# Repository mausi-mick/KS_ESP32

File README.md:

Kennlinienschreiber mit ESP32

Hier möchte ich nur kurz die ESP32-Variante vorstellen.

Die vorher beschriebenen Versionen  -  auf Arduino NANO / ATMega328P   bzw. Arduino-EVERY basierend   - waren im Laufe der Entwicklung in mehrerer Hinsicht an ihre Grenzen gestossen:

    •     zu wenig Speicher
    •     zu wenig Pins
    •     relativ langsam
    •     Bluetooth nur über externe HW (HC05 /HC12)

Die ersten Tests waren dann aber etwas ernüchternd,  

Gerade die verwandten ADC’s (MCP3204) und DAC’s MCP4822 an SPI (VSPI) machten
Probleme., aber das scheint gelöst zu sein.

Ich verwende ein ESP-Modul mit 38 Pins, um möglichst viele Pins zur Verfügung zu haben für
die BUSSE (I2C, SPI), Schalter und Encoder und  RX/TX (z.B. zur Verbindung mit modif. Transistortester)

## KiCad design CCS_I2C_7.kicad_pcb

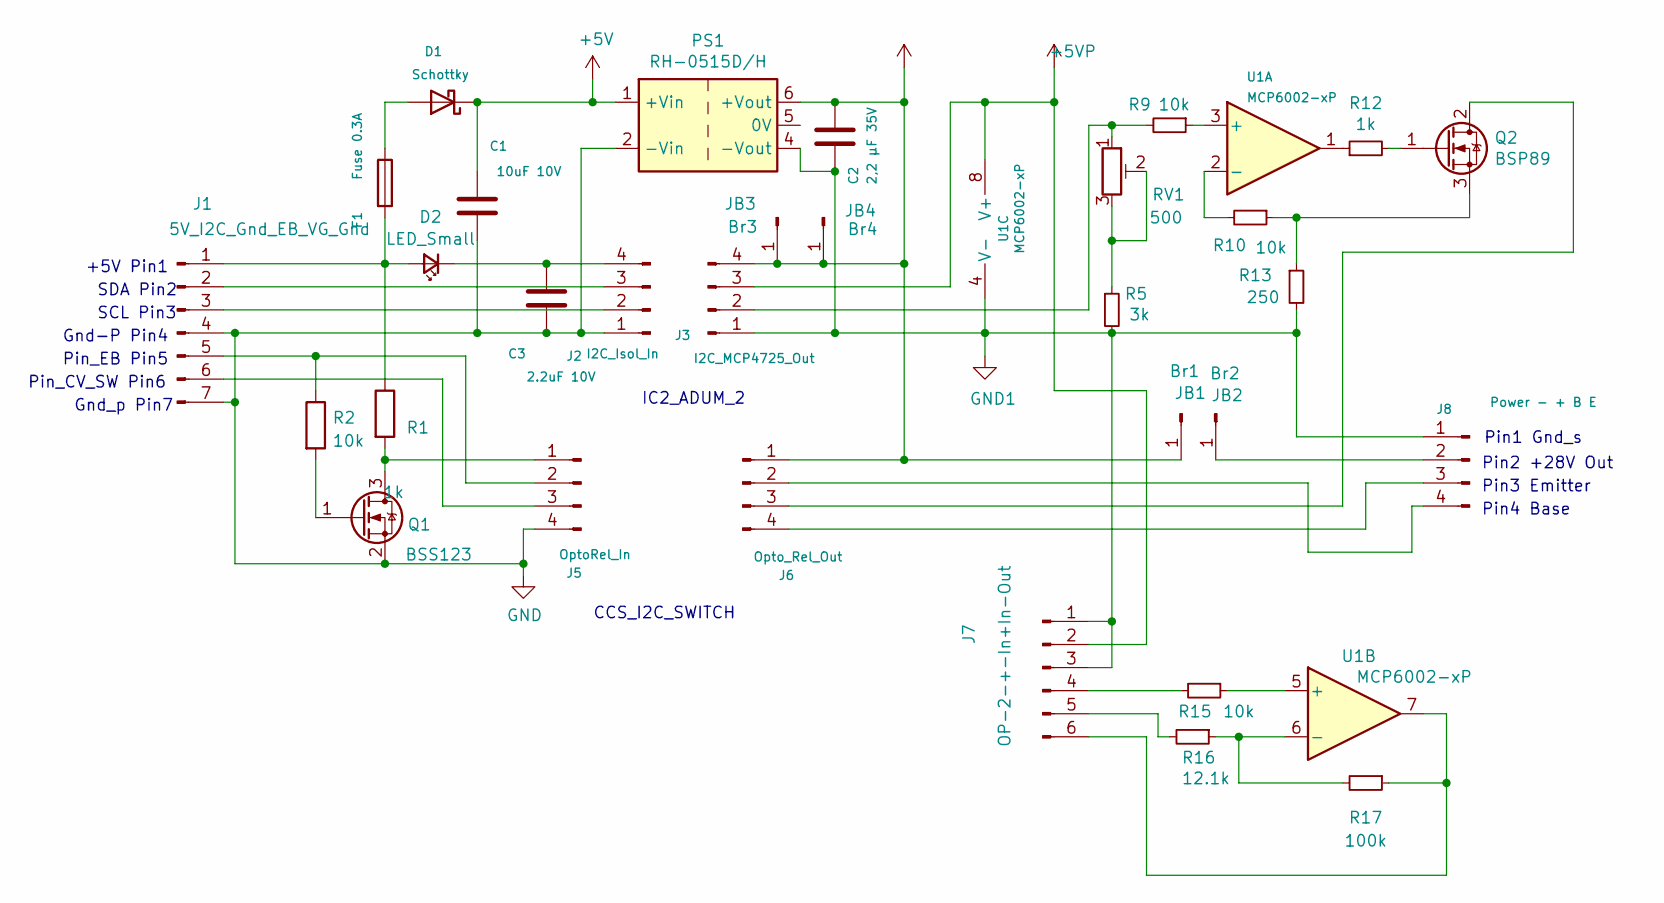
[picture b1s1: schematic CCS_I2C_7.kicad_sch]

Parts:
C1: 10uF 10V; C_1812_4532Metric_Pad1.57x3.40mm_HandSolder
C2: 2,2 µF 35V; C_1812_4532Metric_Pad1.57x3.40mm_HandSolder
C3: 2.2uF 10V; C_1206_3216Metric_Pad1.33x1.80mm_HandSolder
D1: Schottky; D_1206_3216Metric_Pad1.42x1.75mm_HandSolder
D2: LED_Small; LED_D3.0mm
F1: Fuse 0.3A; Fuse_1206_3216Metric_Pad1.42x1.75mm_HandSolder
J1: 5V_I2C_Gnd_EB_VG_Gnd; PinHeader_1x07_P2.54mm_Horizontal
J2: I2C_Isol_In; PinSocket_1x04_P2.54mm_Vertical
J3: I2C_MCP4725_Out; PinSocket_1x04_P2.54mm_Vertical
J5: OptoRel_In; PinSocket_1x04_P2.54mm_Vertical
J6: Opto_Rel_Out; PinSocket_1x04_P2.54mm_Vertical
J7: OP-2-+-In+In-Out; PinHeader_1x06_P2.54mm_Horizontal
J8: Power - + B E; PinHeader_1x04_P2.54mm_Horizontal
JB1: Br1; PinHeader_1x01_P2.54mm_Vertical
JB2: Br2; PinHeader_1x01_P2.54mm_Vertical
JB3: Br3; PinHeader_1x01_P2.54mm_Vertical
JB4: Br4; PinHeader_1x01_P2.54mm_Vertical
PS1: RH-0515D/H; Converter_DCDC_XP_POWER-IHxxxxSH_THT
Q1: BSS123; SOT-23
Q2: BSP89; SOT-223-3_TabPin2
R1: 1k; R_2010_5025Metric_Pad1.40x2.65mm_HandSolder
R2: 10k; R_1206_3216Metric_Pad1.30x1.75mm_HandSolder
R5: 3k; R_Axial_DIN0207_L6.3mm_D2.5mm_P10.16mm_Horizontal
R9, R10, R15: 10k; R_Axial_DIN0207_L6.3mm_D2.5mm_P10.16mm_Horizontal
R12: 1k; R_Axial_DIN0207_L6.3mm_D2.5mm_P10.16mm_Horizontal
R13: 250; R_Axial_DIN0207_L6.3mm_D2.5mm_P10.16mm_Horizontal
R16: 12.1k; R_Axial_DIN0207_L6.3mm_D2.5mm_P10.16mm_Horizontal
R17: 100k; R_Axial_DIN0207_L6.3mm_D2.5mm_P10.16mm_Horizontal
RV1: 500; Potentiometer_ACP_CA6-H2,5_Horizontal
U1: MCP6002-xP; DIP-8_W7.62mm_LongPads

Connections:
+5V: C1.1, D1.1 (K), PS1.1 (+Vin)
+5VP: J3.3, J7.2, U1.8 (V+)
+28V: C2.1, J3.4, J6.1, JB1.1, JB3.1, JB4.1, PS1.6 (+Vout)
GND: C1.2, C3.2, J1.4, J1.7, J2.1, J5.4, PS1.2 (-Vin), Q1.2 (S)
GND1: C2.2, J3.1, J7.1, J7.3, J8.1, PS1.4 (-Vout), R5.2, R13.2, U1.4 (V-)
unnamed: D1.2 (A), F1.1
unnamed: D2.2 (A), F1.2, J1.1, R1.1
unnamed: C3.1, D2.1 (K), J2.4
unnamed: J1.2, J2.3
unnamed: J1.3, J2.2
unnamed: J1.5, J5.2, R2.1
unnamed: J1.6, J5.3
unnamed: J3.2, R9.2, RV1.1
unnamed: J5.1, Q1.3 (D), R1.2
unnamed: J6.2, J8.4
unnamed: J6.3, Q2.2 (D)
unnamed: J6.4, J8.3
unnamed: J7.4, R15.2
unnamed: J7.5, R16.2
unnamed: J7.6, R17.1, U1.7
unnamed: J8.2, JB2.1
unnamed: Q1.1 (G), R2.2
unnamed: Q2.1 (G), R12.2
unnamed: Q2.3 (S), R10.1, R13.1
unnamed: R5.1, RV1.2, RV1.3
unnamed: R12.1, U1.1
unnamed: R9.1, U1.3 (+)
unnamed: R10.2, U1.2 (-)
unnamed: R15.1, U1.5 (+)
unnamed: R16.1, R17.2, U1.6 (-)

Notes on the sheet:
Pin_EB Pin5
IC2_ADUM_2
+5V Pin1
Gnd-P Pin4
SDA Pin2
Pin2 +28V Out
SCL Pin3
Pin4 Base
Gnd_p Pin7
Pin1 Gnd_s
Pin3 Emitter
CCS_I2C_SWITCH
Pin_CV_SW Pin6

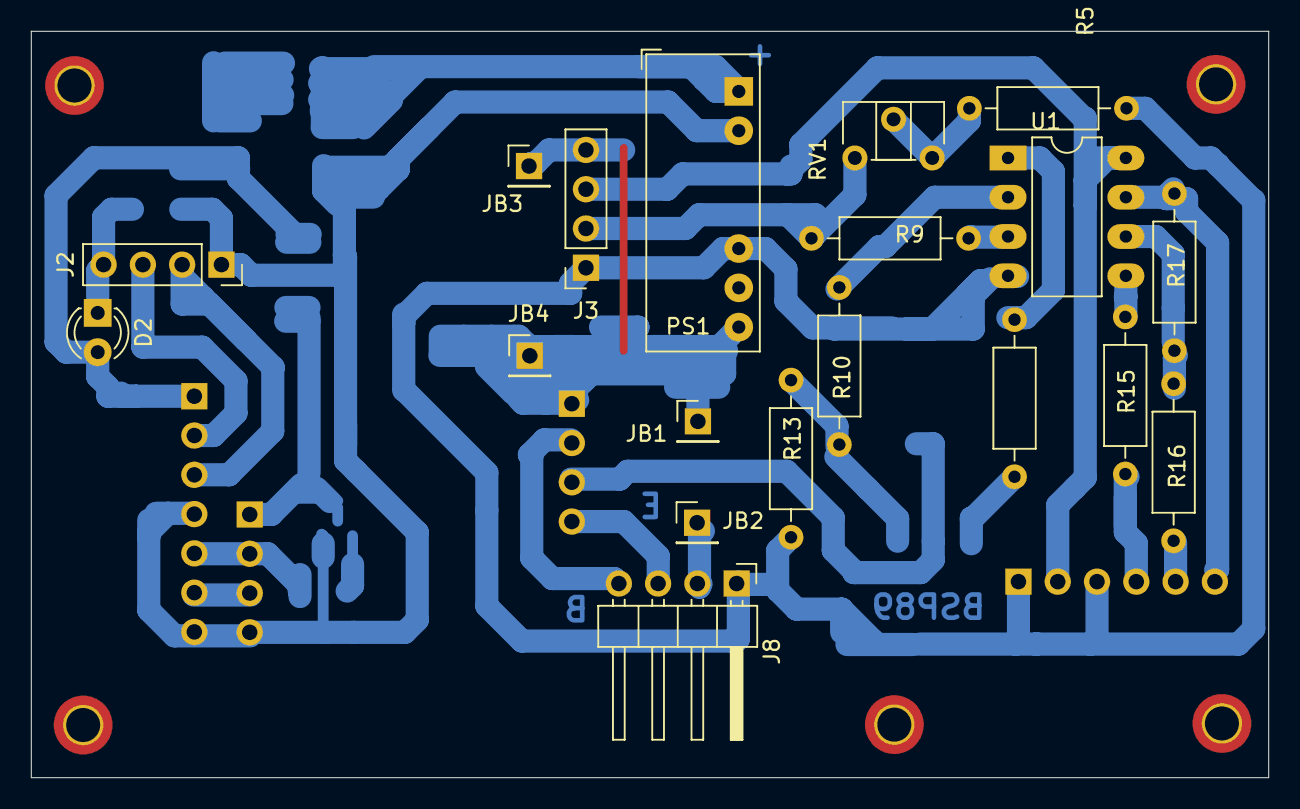
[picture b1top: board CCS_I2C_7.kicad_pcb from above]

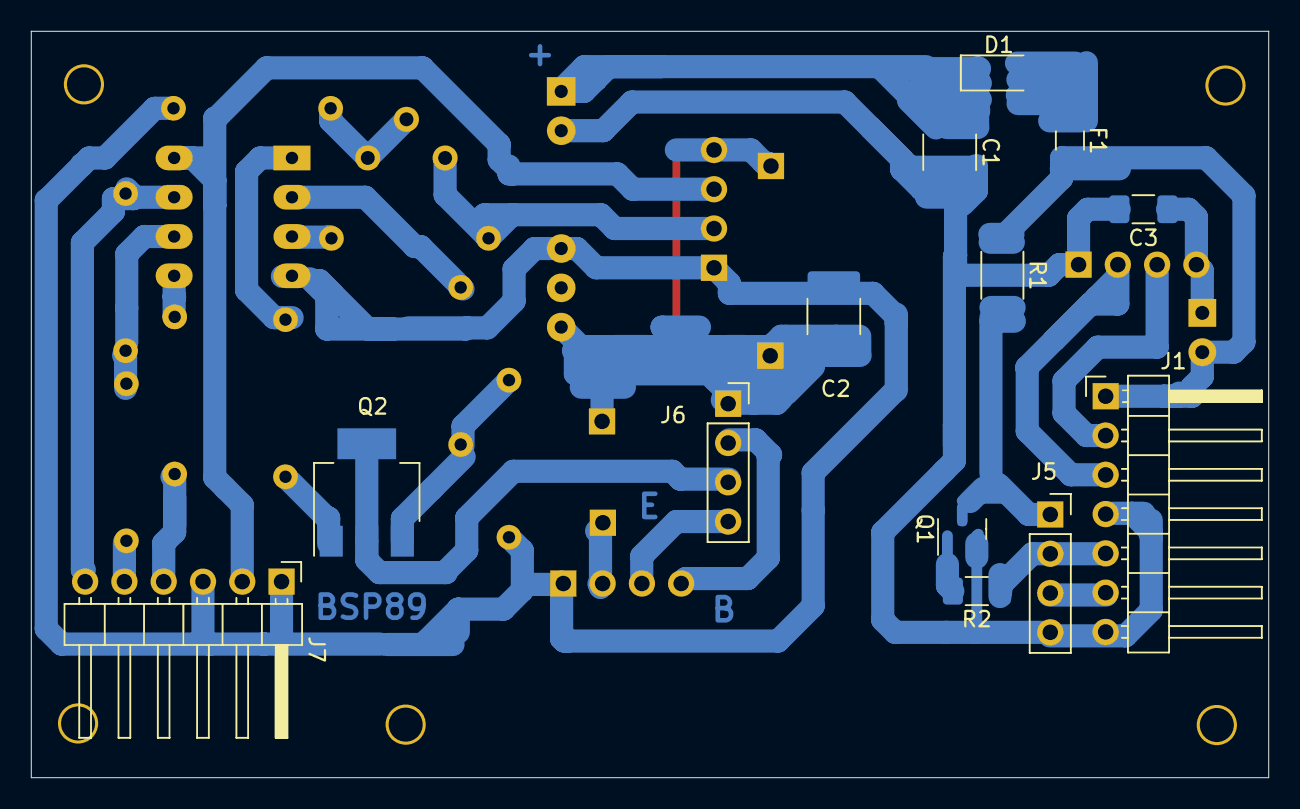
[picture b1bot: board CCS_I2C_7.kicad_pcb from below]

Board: 2 copper layers, 80.0 x 48.3 mm, 32 parts (13 on the bottom side), 30 nets.

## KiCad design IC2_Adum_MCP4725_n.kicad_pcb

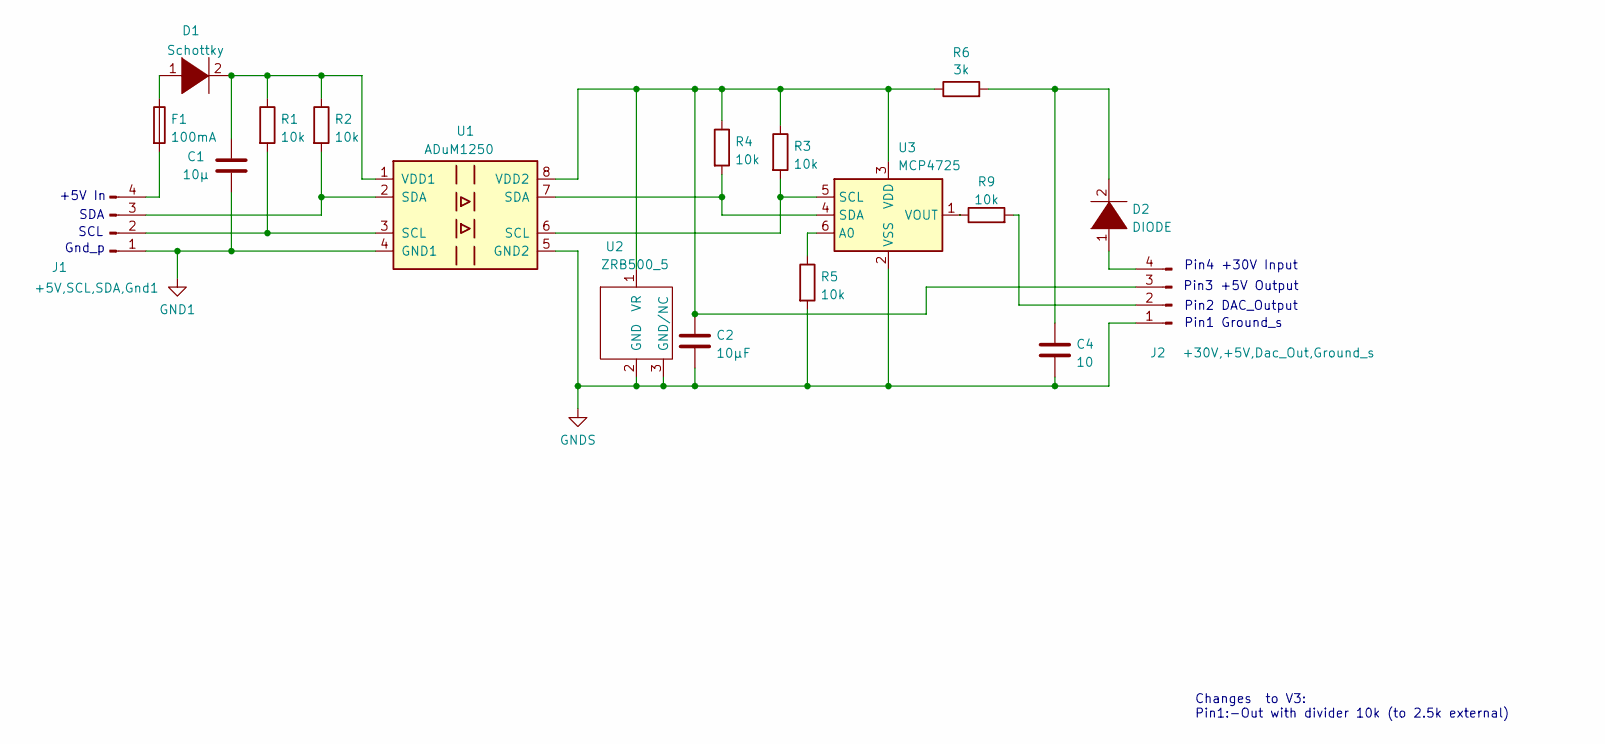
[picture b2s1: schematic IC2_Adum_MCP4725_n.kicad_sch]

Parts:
C1: 10µ; C_1206_3216Metric_Pad1.33x1.80mm_HandSolder
C2: 10µF; C_1206_3216Metric_Pad1.33x1.80mm_HandSolder
C4: 10; C_1206_3216Metric_Pad1.33x1.80mm_HandSolder
D1: Schottky; D_1206_3216Metric_Pad1.42x1.75mm_HandSolder
D2: DIODE; D_0805_2012Metric_Pad1.15x1.40mm_HandSolder
F1: 100mA; Fuse_1206_3216Metric_Pad1.42x1.75mm_HandSolder
J1: +5V,SCL,SDA,Gnd1; PinHeader_1x04_P2.54mm_Vertical
J2: +30V,+5V,Dac_Out,Ground_s; PinHeader_1x04_P2.54mm_Vertical
R1, R2, R3, R4, R5, R9: 10k; R_1206_3216Metric_Pad1.30x1.75mm_HandSolder
R6: 3k; R_1206_3216Metric_Pad1.30x1.75mm_HandSolder
U1: ADuM1250; SOIC-8_3.9x4.9mm_P1.27mm
U2: ZRB500_5; SOT-23-3
U3: MCP4725; SOT-23-6

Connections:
GND1: C1.2, J1.1, U1.4 (GND1)
GNDS: C2.2, C4.2, J2.1, R5.2, U1.5 (GND2), U2.2 (GND), U2.3 (GND/NC), U3.2 (VSS)
unnamed: C1.1, D1.2 (A), R1.1, R2.1, U1.1 (VDD1)
unnamed: D1.1 (K), F1.1
unnamed: C4.1, D2.2 (A), R6.2
unnamed: D2.1 (K), J2.4
unnamed: J1.2, R1.2, U1.3 (SCL)
unnamed: J1.3, R2.2, U1.2 (SDA)
unnamed: F1.2, J1.4
unnamed: J2.2, R9.2
unnamed: C2.1, J2.3, R3.1, R4.1, R6.1, U1.8 (VDD2), U2.1 (VR), U3.3 (VDD)
unnamed: R5.1, U3.6 (A0)
unnamed: R3.2, U1.6 (SCL), U3.5 (SCL)
unnamed: R4.2, U1.7 (SDA), U3.4 (SDA)
unnamed: R9.1, U3.1 (VOUT)

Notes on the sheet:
Pin2 DAC_Output
Changes to V3: Pin1:-Out with divider 10k (to 2.5k external)
+5V In
Pin3 +5V Output
Gnd_p
SDA
Pin1 Ground_s
SCL
Pin4 +30V Input

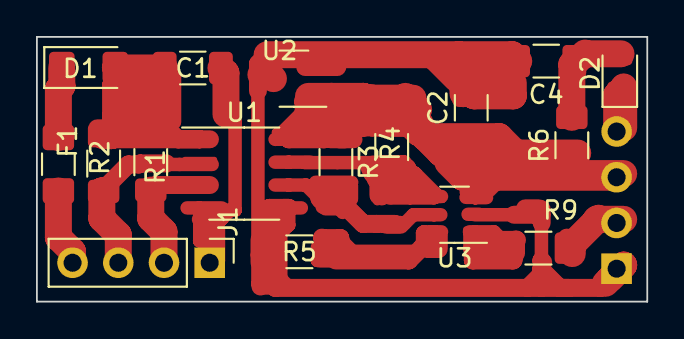
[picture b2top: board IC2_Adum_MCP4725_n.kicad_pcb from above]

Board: 2 copper layers, 33.9 x 14.7 mm, 18 parts (1 on the bottom side), 15 nets.

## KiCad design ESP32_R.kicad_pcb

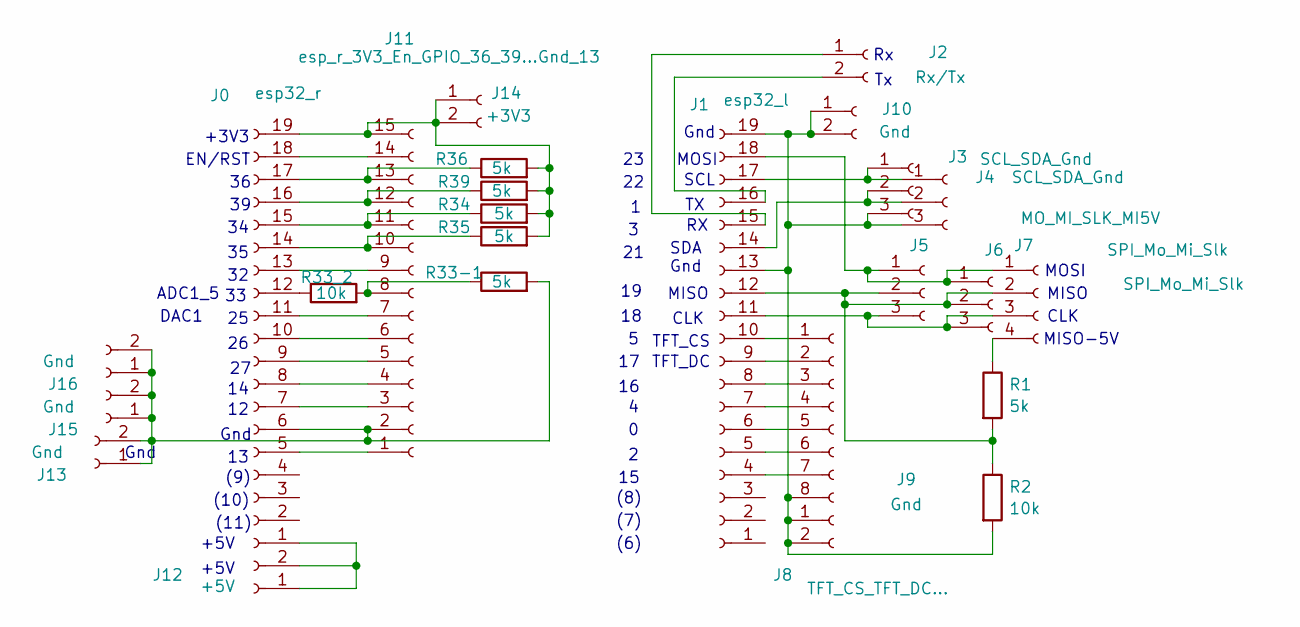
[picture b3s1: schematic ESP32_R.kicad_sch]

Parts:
J0: esp32_r; PinSocket_1x19_P2.54mm_Vertical
J1: esp32_l; PinSocket_1x19_P2.54mm_Vertical
J2: Rx/Tx; PinSocket_1x02_P2.54mm_Vertical
J3, J4: SCL_SDA_Gnd; PinSocket_1x03_P2.54mm_Vertical
J5, J6: SPI_Mo_Mi_Slk; PinSocket_1x03_P2.54mm_Vertical
J7: MO_MI_SLK_MI5V; PinHeader_1x04_P2.54mm_Vertical
J8: TFT_CS_TFT_DC...; PinSocket_1x08_P2.54mm_Vertical
J9, J10, J13, J15, J16: Gnd; PinSocket_1x02_P2.54mm_Vertical
J11: esp_r_3V3_En_GPIO_36_39...Gnd_13; PinHeader_1x15_P2.54mm_Vertical
J12: +5V; PinSocket_1x02_P2.54mm_Vertical
J14: +3V3; PinSocket_1x02_P2.54mm_Vertical
R1, R33-1, R34, R35, R36, R39: 5k; R_1206_3216Metric_Pad1.30x1.75mm_HandSolder
R2: 10k; R_1206_3216Metric_Pad1.30x1.75mm_HandSolder
R33_2: 10k; R_0603_1608Metric_Pad0.98x0.95mm_HandSolder

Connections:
unnamed: J0.1, J12.1, J12.2
unnamed: J0.5, J11.1
unnamed: J0.6, J11.2, J13.1, J13.2, J15.1, J15.2, J16.1, J16.2, R33-1.2
unnamed: J0.7, J11.3
unnamed: J0.8, J11.4
unnamed: J0.9, J11.5
unnamed: J0.10, J11.6
unnamed: J0.11, J11.7
unnamed: J0.12, R33_2.1
unnamed: J0.13, J11.9
unnamed: J0.14, J11.10, R35.1
unnamed: J0.15, J11.11, R34.1
unnamed: J0.16, J11.12, R39.1
unnamed: J0.17, J11.13, R36.1
unnamed: J0.18, J11.14
unnamed: J0.19, J11.15, J14.1, J14.2, R34.2, R35.2, R36.2, R39.2
unnamed: J1.4, J8.7
unnamed: J1.5, J8.6
unnamed: J1.6, J8.5
unnamed: J1.7, J8.4
unnamed: J1.8, J8.3
unnamed: J1.9, J8.2
unnamed: J1.10, J8.1
unnamed: J1.11, J5.3, J6.3, J7.3
unnamed: J1.12, J5.2, J6.2, J7.2, R1.2, R2.1
unnamed: J1.13, J1.19, J3.3, J4.3, J8.8, J9.1, J9.2, J10.1, J10.2, R2.2
unnamed: J1.14, J3.2, J4.2
unnamed: J1.15, J2.1
unnamed: J1.16, J2.2
unnamed: J1.17, J3.1, J4.1
unnamed: J1.18, J5.1, J6.1, J7.1
unnamed: J7.4, R1.1
unnamed: J11.8, R33-1.1, R33_2.2

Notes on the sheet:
Gnd
EN/RST
MOSI
TFT_CS
(10)
ADC1_5
MISO-5V
CLK
(6)
DAC1
(7)
(11)
TFT_DC
MISO
(8)
(9)
SDA
SCL
+3V3
+5V

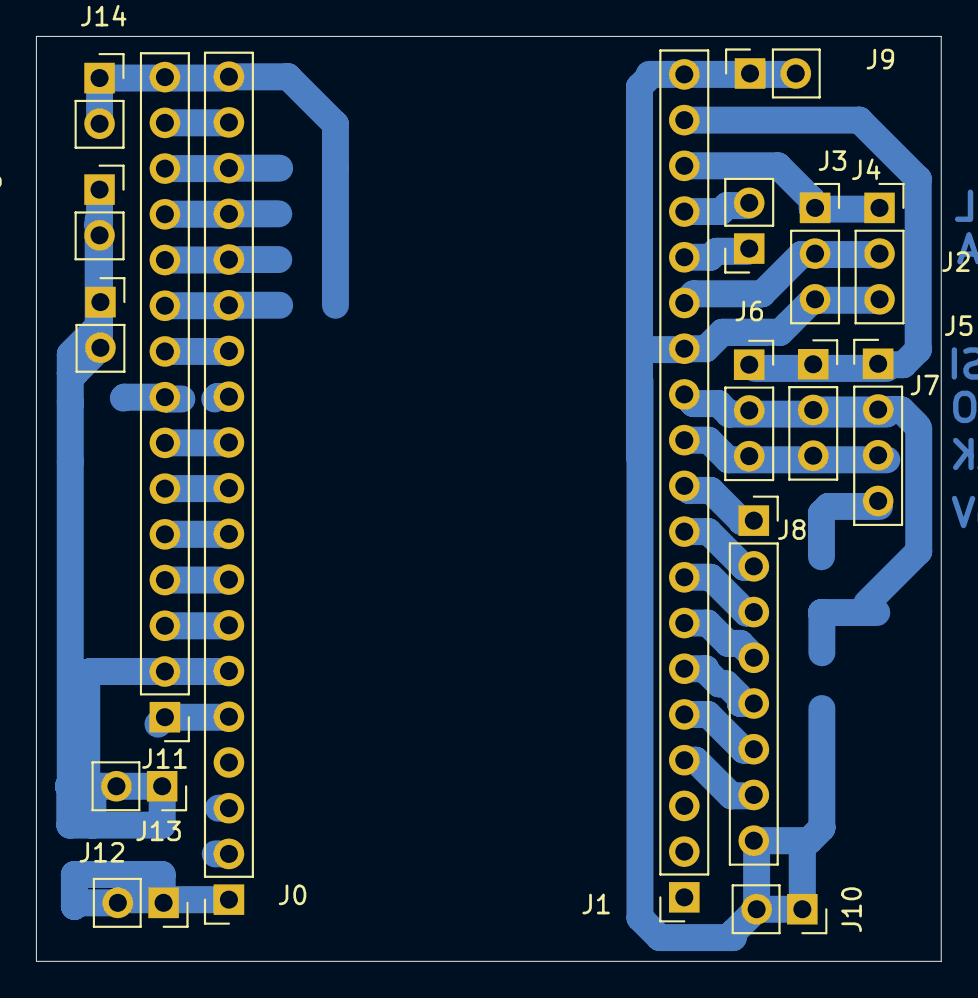
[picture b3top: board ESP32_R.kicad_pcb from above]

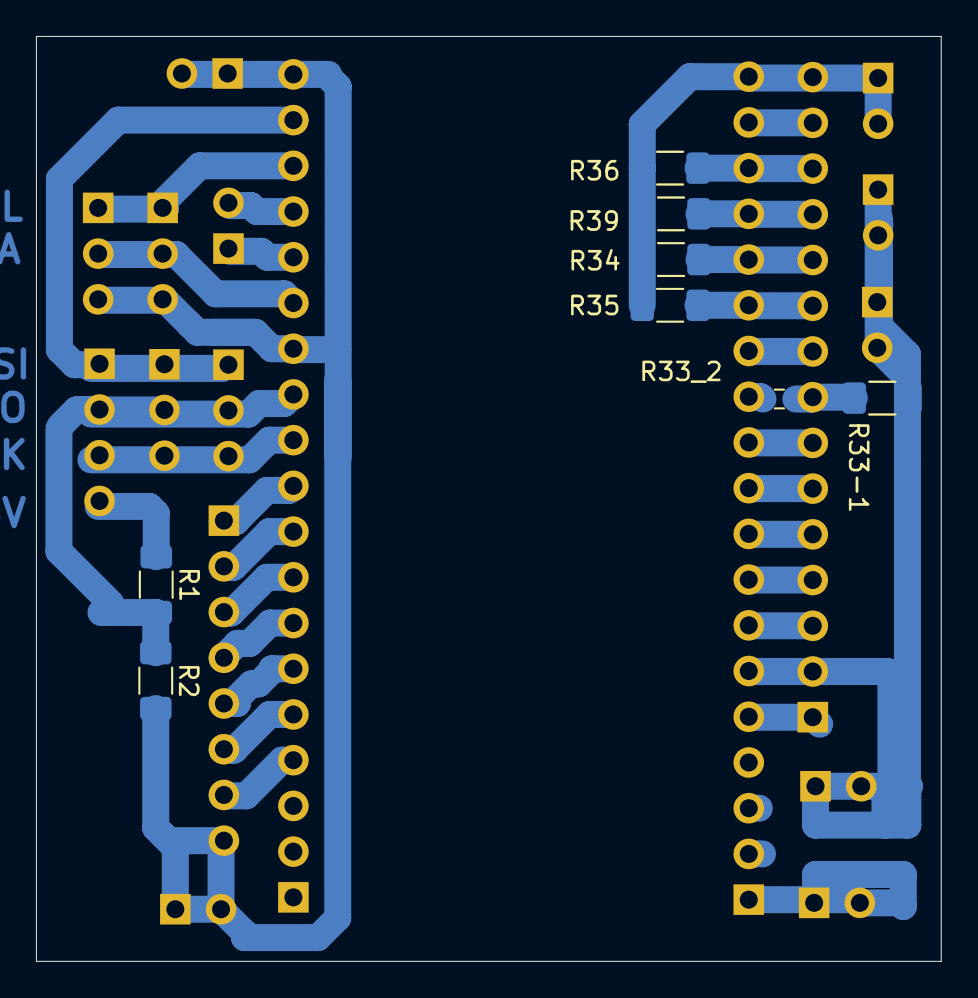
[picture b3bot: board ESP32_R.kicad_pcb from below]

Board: 2 copper layers, 50.3 x 51.4 mm, 25 parts (8 on the bottom side), 33 nets.

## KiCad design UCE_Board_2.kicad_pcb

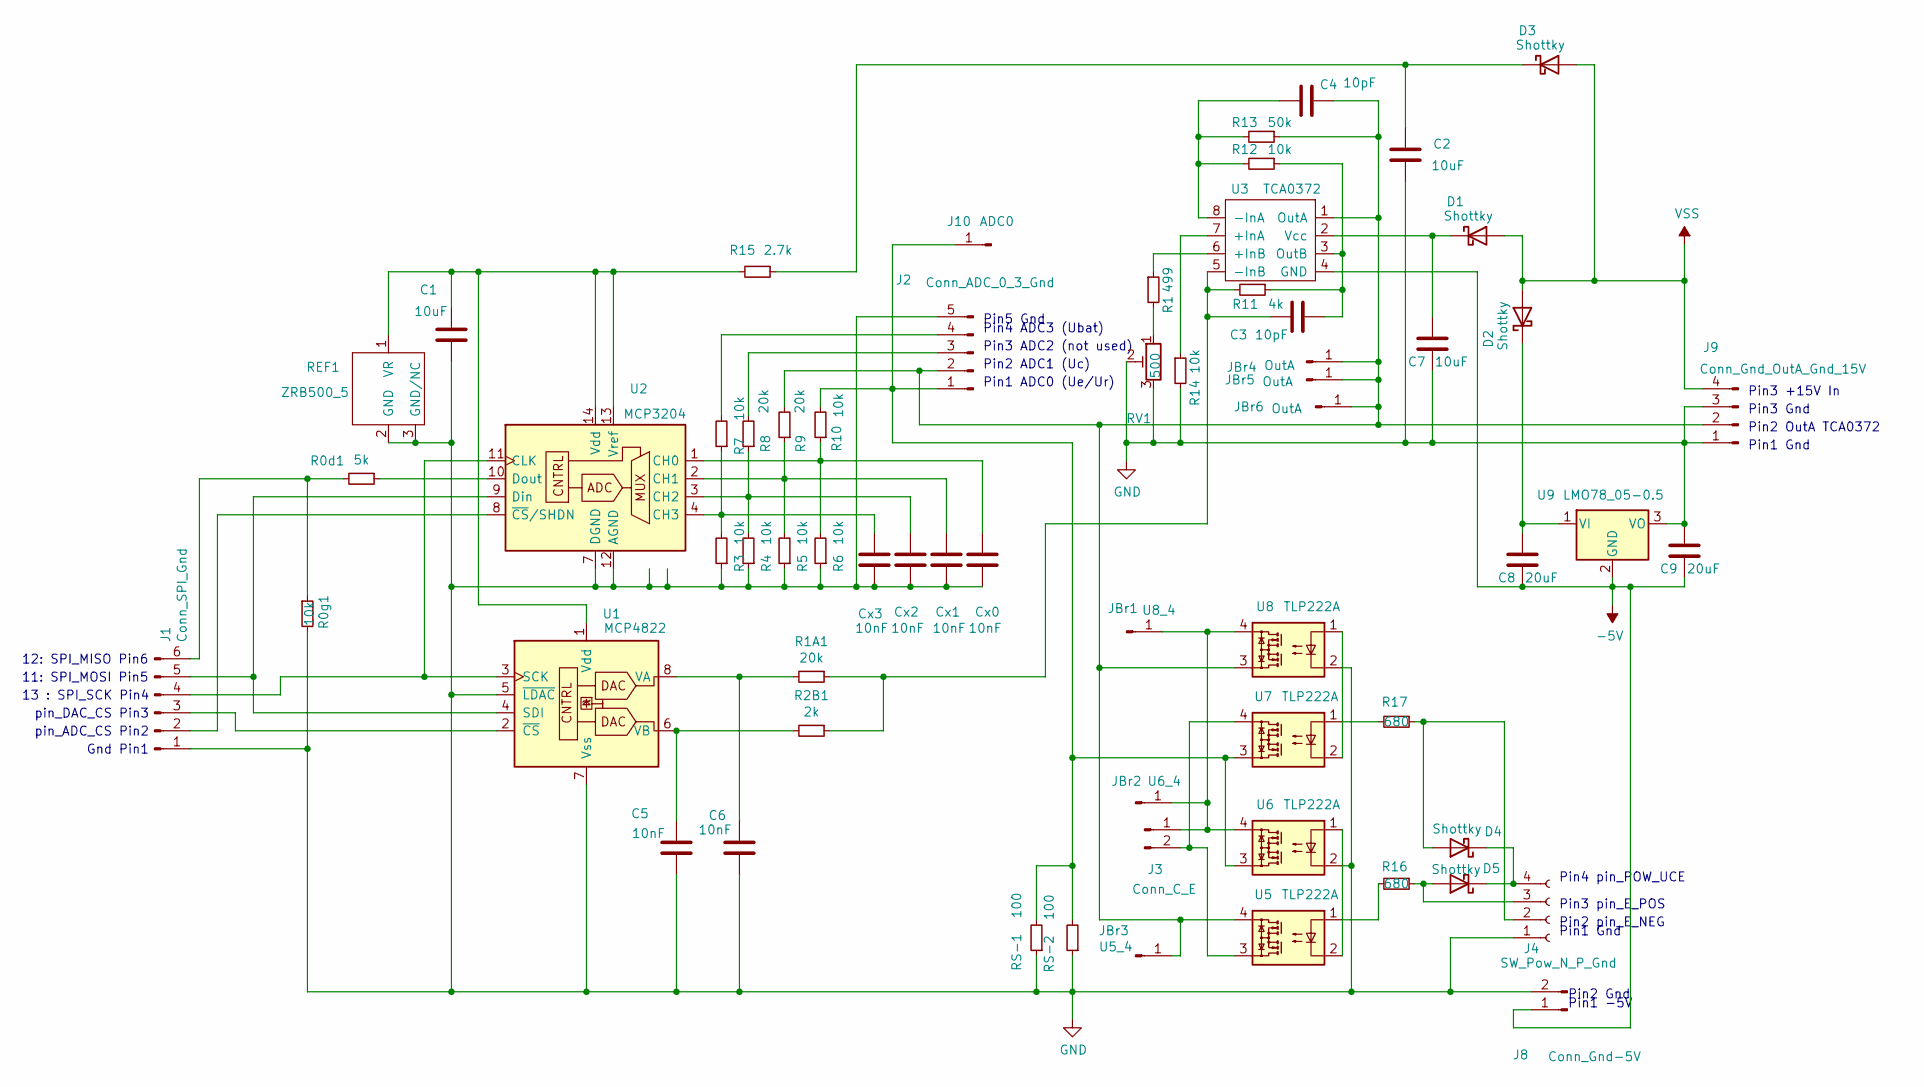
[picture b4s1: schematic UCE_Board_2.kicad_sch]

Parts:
C1: 10uF; C_1210_3225Metric_Pad1.33x2.70mm_HandSolder
C2: 10uF; C_1812_4532Metric_Pad1.57x3.40mm_HandSolder
C3: 10pF; C_Axial_L5.1mm_D3.1mm_P7.50mm_Horizontal
C4: 10pF; C_Rect_L9.0mm_W2.5mm_P7.50mm_MKT
C5, C6: 10nF; C_1206_3216Metric_Pad1.33x1.80mm_HandSolder
C7: 10uF; C_1206_3216Metric_Pad1.33x1.80mm_HandSolder
C8, C9: 20uF; C_1812_4532Metric_Pad1.57x3.40mm_HandSolder
Cx0, Cx1, Cx2, Cx3: 10nF; C_0805_2012Metric_Pad1.18x1.45mm_HandSolder
D1, D2, D3: Shottky; D_1206_3216Metric_Pad1.42x1.75mm_HandSolder
D4, D5: Shottky; D_0603_1608Metric_Pad1.05x0.95mm_HandSolder
J1: Conn_SPI_Gnd; PinHeader_1x06_P2.54mm_Horizontal
J2: Conn_ADC_0_3_Gnd; PinHeader_1x05_P2.54mm_Vertical
J3: Conn_C_E; PinHeader_1x02_P2.54mm_Horizontal
J4: SW_Pow_N_P_Gnd; PinHeader_1x04_P2.54mm_Horizontal
J8: Conn_Gnd-5V; PinHeader_1x02_P2.54mm_Vertical
J9: Conn_Gnd_OutA_Gnd_15V; PinHeader_1x04_P2.54mm_Horizontal
J10: ADC0; PinHeader_1x01_P2.54mm_Vertical
JBr1: U8_4; PinHeader_1x01_P2.54mm_Vertical
JBr2: U6_4; PinHeader_1x01_P2.54mm_Vertical
JBr3: U5_4; PinHeader_1x01_P1.00mm_Vertical
JBr4: OutA; PinHeader_1x01_P1.00mm_Vertical
JBr5, JBr6: OutA; PinHeader_1x01_P1.27mm_Vertical
R0d1: 5k; R_1206_3216Metric_Pad1.30x1.75mm_HandSolder
R0g1, R12: 10k; R_Axial_DIN0204_L3.6mm_D1.6mm_P7.62mm_Horizontal
R1: 499; R_Axial_DIN0207_L6.3mm_D2.5mm_P10.16mm_Horizontal
R1A1: 20k; R_Axial_DIN0207_L6.3mm_D2.5mm_P10.16mm_Horizontal
R2B1: 2k; R_Axial_DIN0207_L6.3mm_D2.5mm_P10.16mm_Horizontal
R3, R4, R5, R6, R7, R10: 10k; R_1206_3216Metric_Pad1.30x1.75mm_HandSolder
R8, R9: 20k; R_1206_3216Metric_Pad1.30x1.75mm_HandSolder
R11: 4k; R_Axial_DIN0207_L6.3mm_D2.5mm_P10.16mm_Horizontal
R13: 50k; R_Axial_DIN0207_L6.3mm_D2.5mm_P10.16mm_Horizontal
R14: 10k; R_Axial_DIN0207_L6.3mm_D2.5mm_P10.16mm_Horizontal
R15: 2.7k; R_Axial_DIN0207_L6.3mm_D2.5mm_P10.16mm_Horizontal
R16, R17: 680; R_Axial_DIN0207_L6.3mm_D2.5mm_P10.16mm_Horizontal
REF1: ZRB500_5; SOT-23
RS-1, RS-2: 100; R_Axial_DIN0207_L6.3mm_D2.5mm_P10.16mm_Horizontal
RV1: 500; Potentiometer_ACP_CA9-H2,5_Horizontal
U1: MCP4822; DIP-8_W7.62mm_LongPads
U2: MCP3204; DIP-14_W7.62mm
U3: TCA0372; DIP-8_W7.62mm_LongPads
U5, U6, U7, U8: TLP222A; DIP-4_W7.62mm
U9: LMO78_05-0.5; TO-220-3_Vertical

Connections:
-5V: C8.2, C9.2, J8.1, U3.4 (GND), U9.2 (GND)
GND: C1.2, C2.2, C5.1, C6.1, C7.2, C9.1, Cx0.1, Cx1.1, Cx2.1, Cx3.1, J1.1, J2.5, J4.1, J8.2, J9.1, J9.3, R0g1.2, R3.1, R4.1, R5.1, R6.1, R14.2, REF1.2 (GND), REF1.3 (GND/NC), RS-1.1, RS-2.1, RV1.2, RV1.3, U1.5 (~LDAC), U1.7 (Vss), U2.5 (NC), U2.6 (NC), U2.7 (DGND), U2.12 (AGND), U6.2, U8.2, U9.3 (VO)
unnamed: C7.1, D1.1 (K), U3.2 (Vcc)
unnamed: C8.1, D2.1 (K), U9.1 (VI)
unnamed: C2.1, D3.1 (K), R15.1
unnamed: D4.2 (A), J4.2, R17.1
unnamed: D4.1 (K), D5.1 (K), J4.4
unnamed: D5.2 (A), J4.3, R16.1
unnamed: J1.2, U2.8 (~CS/SHDN)
unnamed: J1.3, U1.2 (~CS)
unnamed: J1.4, U1.3 (SCK), U2.11 (CLK)
unnamed: J1.5, U1.4 (SDI), U2.9 (Din)
unnamed: J1.6, R0d1.2, R0g1.1
unnamed: C4.1, J2.2, J9.2, JBr3.1, JBr4.1, JBr5.1, JBr6.1, R9.2, R13.1, U3.1 (OutA), U5.4, U8.3
unnamed: J2.3, R8.2
unnamed: J2.4, R7.2
unnamed: J3.1, JBr1.1, JBr2.1, U6.4, U8.4
unnamed: J3.2, U5.3, U7.4
unnamed: J2.1, J10.1, R10.2, RS-1.2, RS-2.2, U6.3, U7.3
unnamed: R1.2, RV1.1
unnamed: R16.2, U5.1
unnamed: R17.2, U7.1
unnamed: C1.1, R15.2, REF1.1 (VR), U1.1 (Vdd), U2.13 (Vref), U2.14 (Vdd)
unnamed: C6.2, R1A1.2, U1.8 (VA)
unnamed: C5.2, R2B1.2, U1.6 (VB)
unnamed: Cx0.2, R6.2, R10.1, U2.1 (CH0)
unnamed: Cx1.2, R5.2, R9.1, U2.2 (CH1)
unnamed: Cx2.2, R4.2, R8.1, U2.3 (CH2)
unnamed: Cx3.2, R3.2, R7.1, U2.4 (CH3)
unnamed: R0d1.1, U2.10 (Dout)
unnamed: R14.1, U3.7 (+InA)
unnamed: R1.1, U3.6 (+InB)
unnamed: C4.2, R12.2, R13.2, U3.8 (-InA)
unnamed: C3.2, R1A1.1, R2B1.1, R11.2, U3.5 (-InB)
unnamed: C3.1, R11.1, R12.1, U3.3 (OutB)
unnamed: U5.2, U6.1
unnamed: U7.2, U8.1
VSS: D1.2 (A), D2.2 (A), D3.2 (A), J9.4

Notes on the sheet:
pin_ADC_CS Pin2
Pin1 Gnd
Pin5 Gnd
Gnd Pin1
Pin2 pin_E_NEG
Pin2 OutA TCA0372
Pin4 pin_POW_UCE
12: SPI_MISO Pin6
Pin2 ADC1 (Uc)
pin_DAC_CS Pin3
Pin3 pin_E_POS
Pin3 ADC2 (not used)
Pin2 Gnd
Pin1 ADC0 (Ue/Ur)
Pin3 +15V In
Pin1 -5V
Pin3 Gnd
11: SPI_MOSI Pin5
Pin4 ADC3 (Ubat)
13 : SPI_SCK Pin4

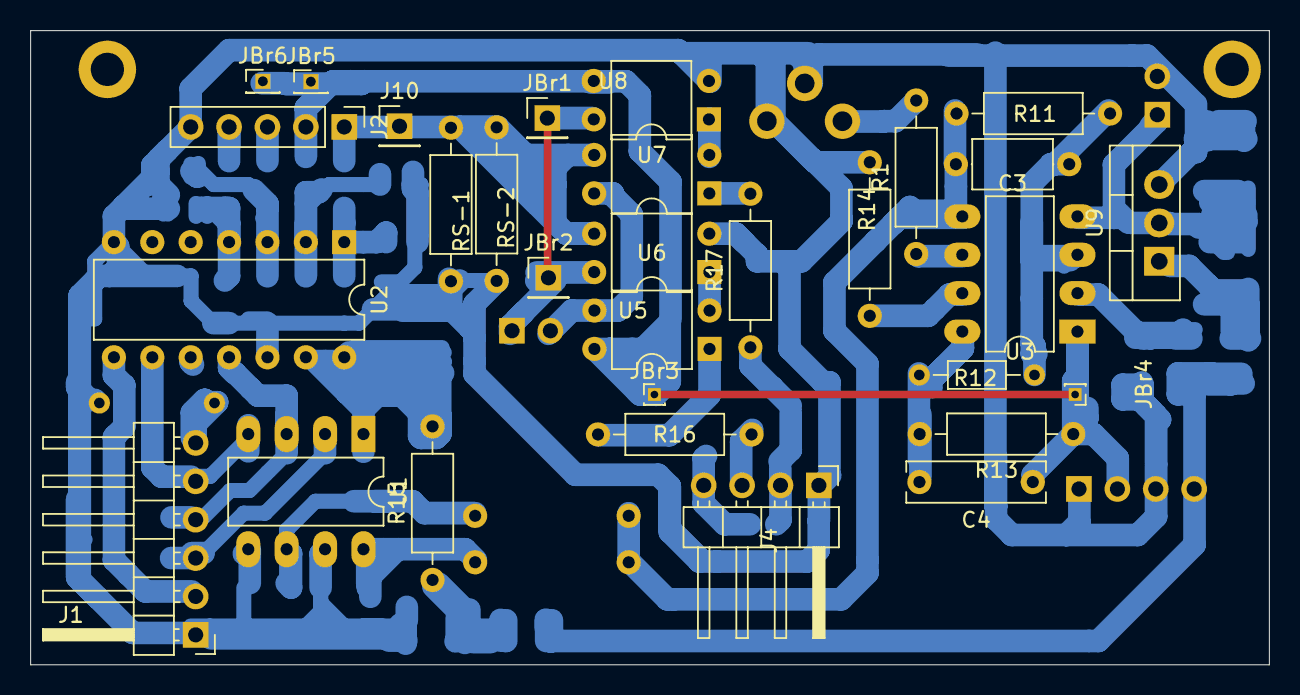
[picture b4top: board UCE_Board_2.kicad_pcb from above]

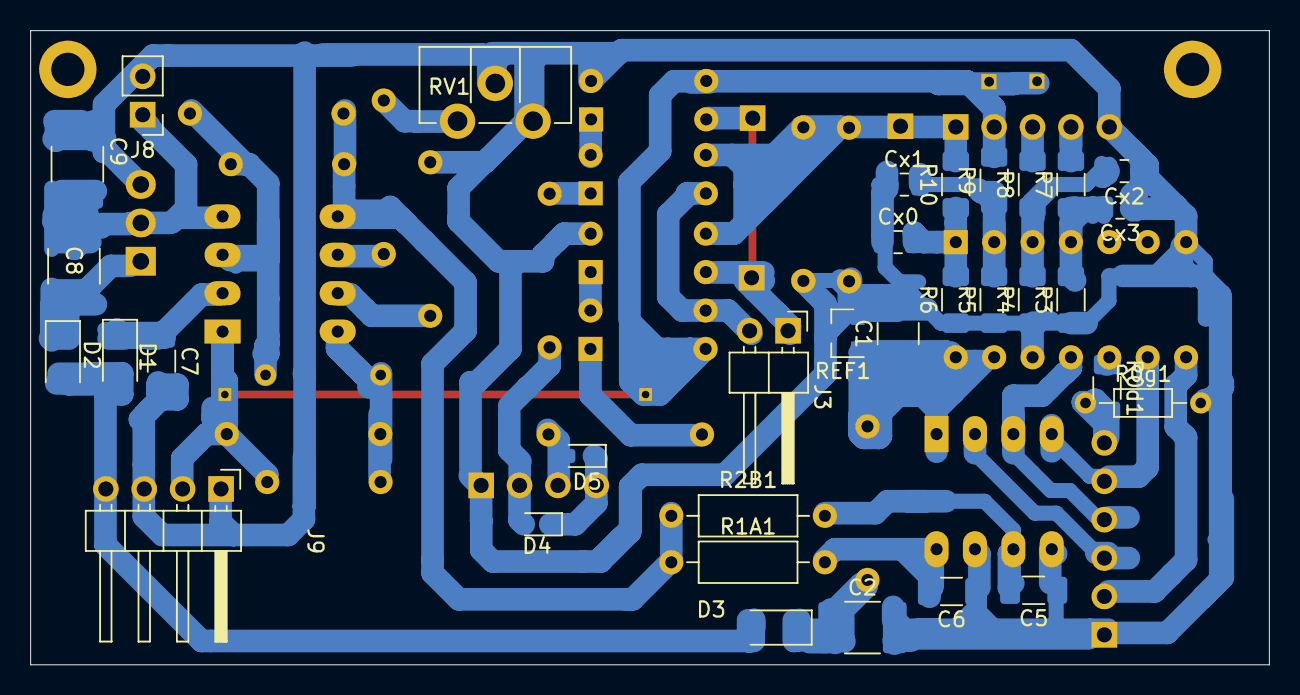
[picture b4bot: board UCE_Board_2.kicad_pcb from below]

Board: 2 copper layers, 82.0 x 42.0 mm, 63 parts (33 on the bottom side), 38 nets.

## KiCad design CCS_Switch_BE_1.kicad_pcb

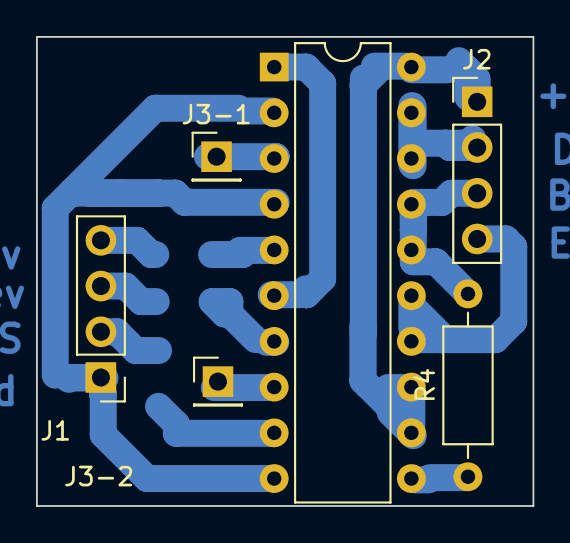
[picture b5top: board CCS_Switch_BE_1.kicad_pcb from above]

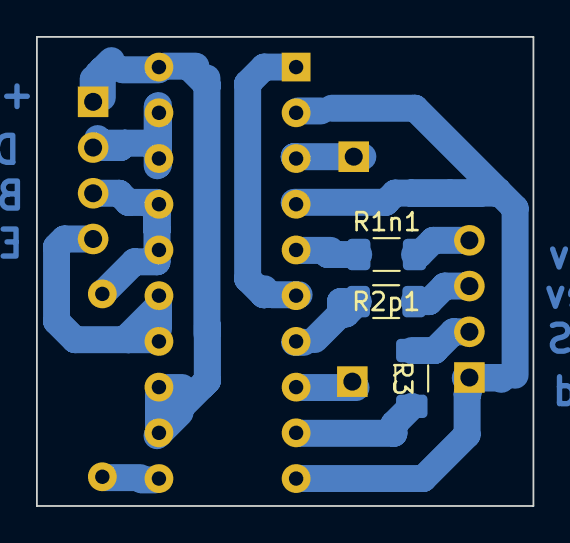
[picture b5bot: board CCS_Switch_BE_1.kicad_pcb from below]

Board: 2 copper layers, 27.6 x 26.1 mm, 9 parts (3 on the bottom side), 4 nets.

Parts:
DIL20: DIP-20_W7.62mm
J1: Switch n,p,Rg,Gndp; PinHeader_1x04_P2.54mm_Vertical
J2: Switch +30V,Drain-CCS,B,E; PinHeader_1x04_P2.54mm_Vertical
J3-1, J3-2: Br; PinHeader_1x01_P2.54mm_Vertical
R1n1, R2p1: 270; R_1206_3216Metric_Pad1.30x1.75mm_HandSolder
R3: 510; R_1206_3216Metric_Pad1.30x1.75mm_HandSolder
R4: 10k; R_Axial_DIN0207_L6.3mm_D2.5mm_P10.16mm_Horizontal

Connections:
unnamed: J1.2, R3.1
unnamed: J1.3, R2p1.1
unnamed: J1.4, R1n1.2
unnamed: J2.3, R4.2

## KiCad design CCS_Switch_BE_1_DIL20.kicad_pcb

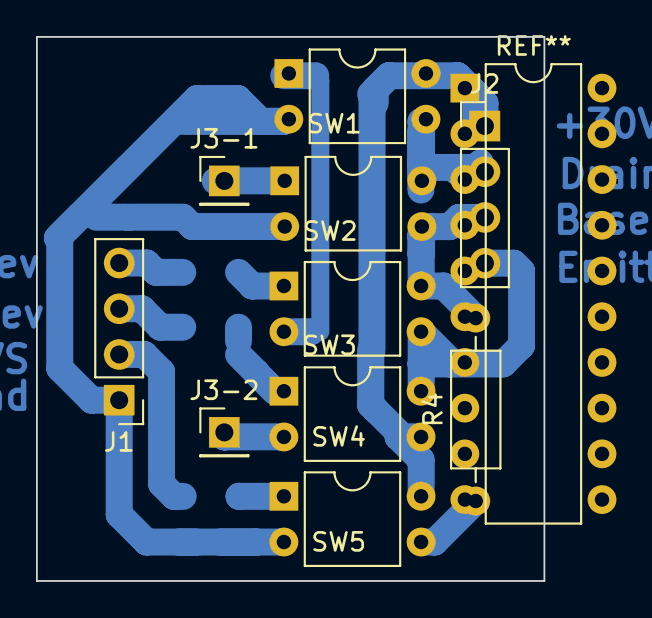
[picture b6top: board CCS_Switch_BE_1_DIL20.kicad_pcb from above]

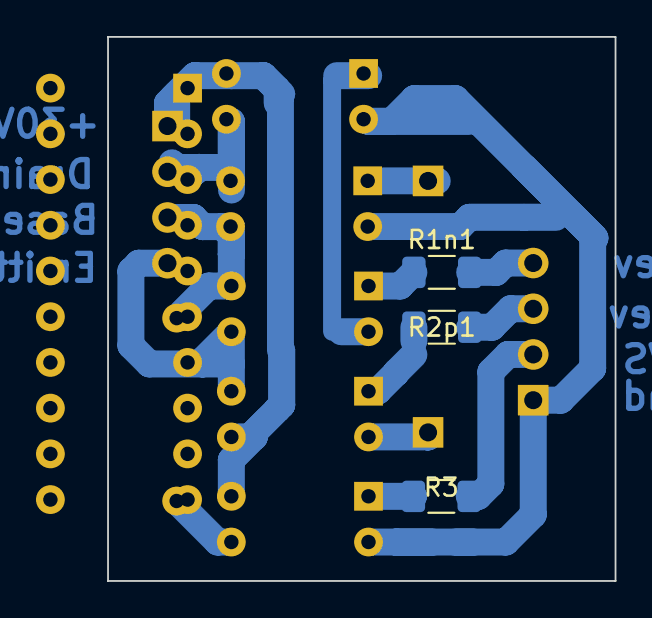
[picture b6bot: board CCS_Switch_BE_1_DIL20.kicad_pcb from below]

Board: 2 copper layers, 28.2 x 30.2 mm, 13 parts (3 on the bottom side), 15 nets.

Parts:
J1: Switch n,p,Rg,Gndp; PinHeader_1x04_P2.54mm_Vertical
J2: Switch +30V,Drain-CCS,B,E; PinHeader_1x04_P2.54mm_Vertical
J3-1, J3-2: Br; PinHeader_1x01_P2.54mm_Vertical
R1n1, R2p1: 270; R_1206_3216Metric_Pad1.30x1.75mm_HandSolder
R3: 510; R_1206_3216Metric_Pad1.30x1.75mm_HandSolder
R4: 10k; R_Axial_DIN0207_L6.3mm_D2.5mm_P10.16mm_Horizontal
SW1, SW2, SW3, SW4, SW5: TLP222A; DIP-4_W7.62mm

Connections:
GND: J1.1, SW1.2, SW2.2, SW5.2
unnamed: J1.2, R3.1
unnamed: J1.3, R2p1.1
unnamed: J1.4, R1n1.2
unnamed: J2.1, SW1.4, SW4.3, SW5.4
unnamed: J2.2, SW1.3, SW2.4
unnamed: J2.3, R4.2, SW2.3, SW3.4
unnamed: J2.4, SW3.3, SW4.4
unnamed: J3-1.1, SW2.1
unnamed: J3-2.1, SW4.2
unnamed: R1n1.1, SW3.1
unnamed: R2p1.2, SW4.1
unnamed: R3.2, SW5.1
unnamed: R4.1, SW5.3
unnamed: SW1.1, SW3.2

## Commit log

2024-04-19 Create README.md
    Kennlinienschreiber mit ESP32
    Hier möchte ich nur kurz die ESP32-Variante vorstellen.
    Die vorher beschriebenen Versionen - auf Arduino NANO / ATMega328P bzw. Arduino-EVERY basierend - waren im Laufe der Entwicklung in mehrerer Hinsicht an ihre Grenzen gestossen:
    • zu wenig Speicher
    • zu wenig Pins
    • relativ langsam
2024-08-06 Add files via upload
    CurveTracer with Touch-Menu
